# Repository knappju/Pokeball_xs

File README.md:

# __Pokeball_xs__
## __Project Info__

__Created:__                        August 10, 2022

__Project Version:__                v 0.0.0.2  

__Stable Branch:__                  master

### __Code__
* __IDE:__ MPLAB X IDE v5.50

__Last Release Date:__              August 21, 2022  
__Last Stable Release:__            v 0.0.0.2 

### __ECAD__
* __CAD:__ KiCAD v6.0

__Last Release Date:__              August 21, 2022  
__Last Stable Release:__            v 0.0.0.2

## Versioning

For the versions available, see the [tags on this repository](https://github.com/knappju/Pokeball_xs/commits/master). 
## Authors

* **Justin Knapp** - *Circuit Design, PCB Design, Code, Mechanical Design*

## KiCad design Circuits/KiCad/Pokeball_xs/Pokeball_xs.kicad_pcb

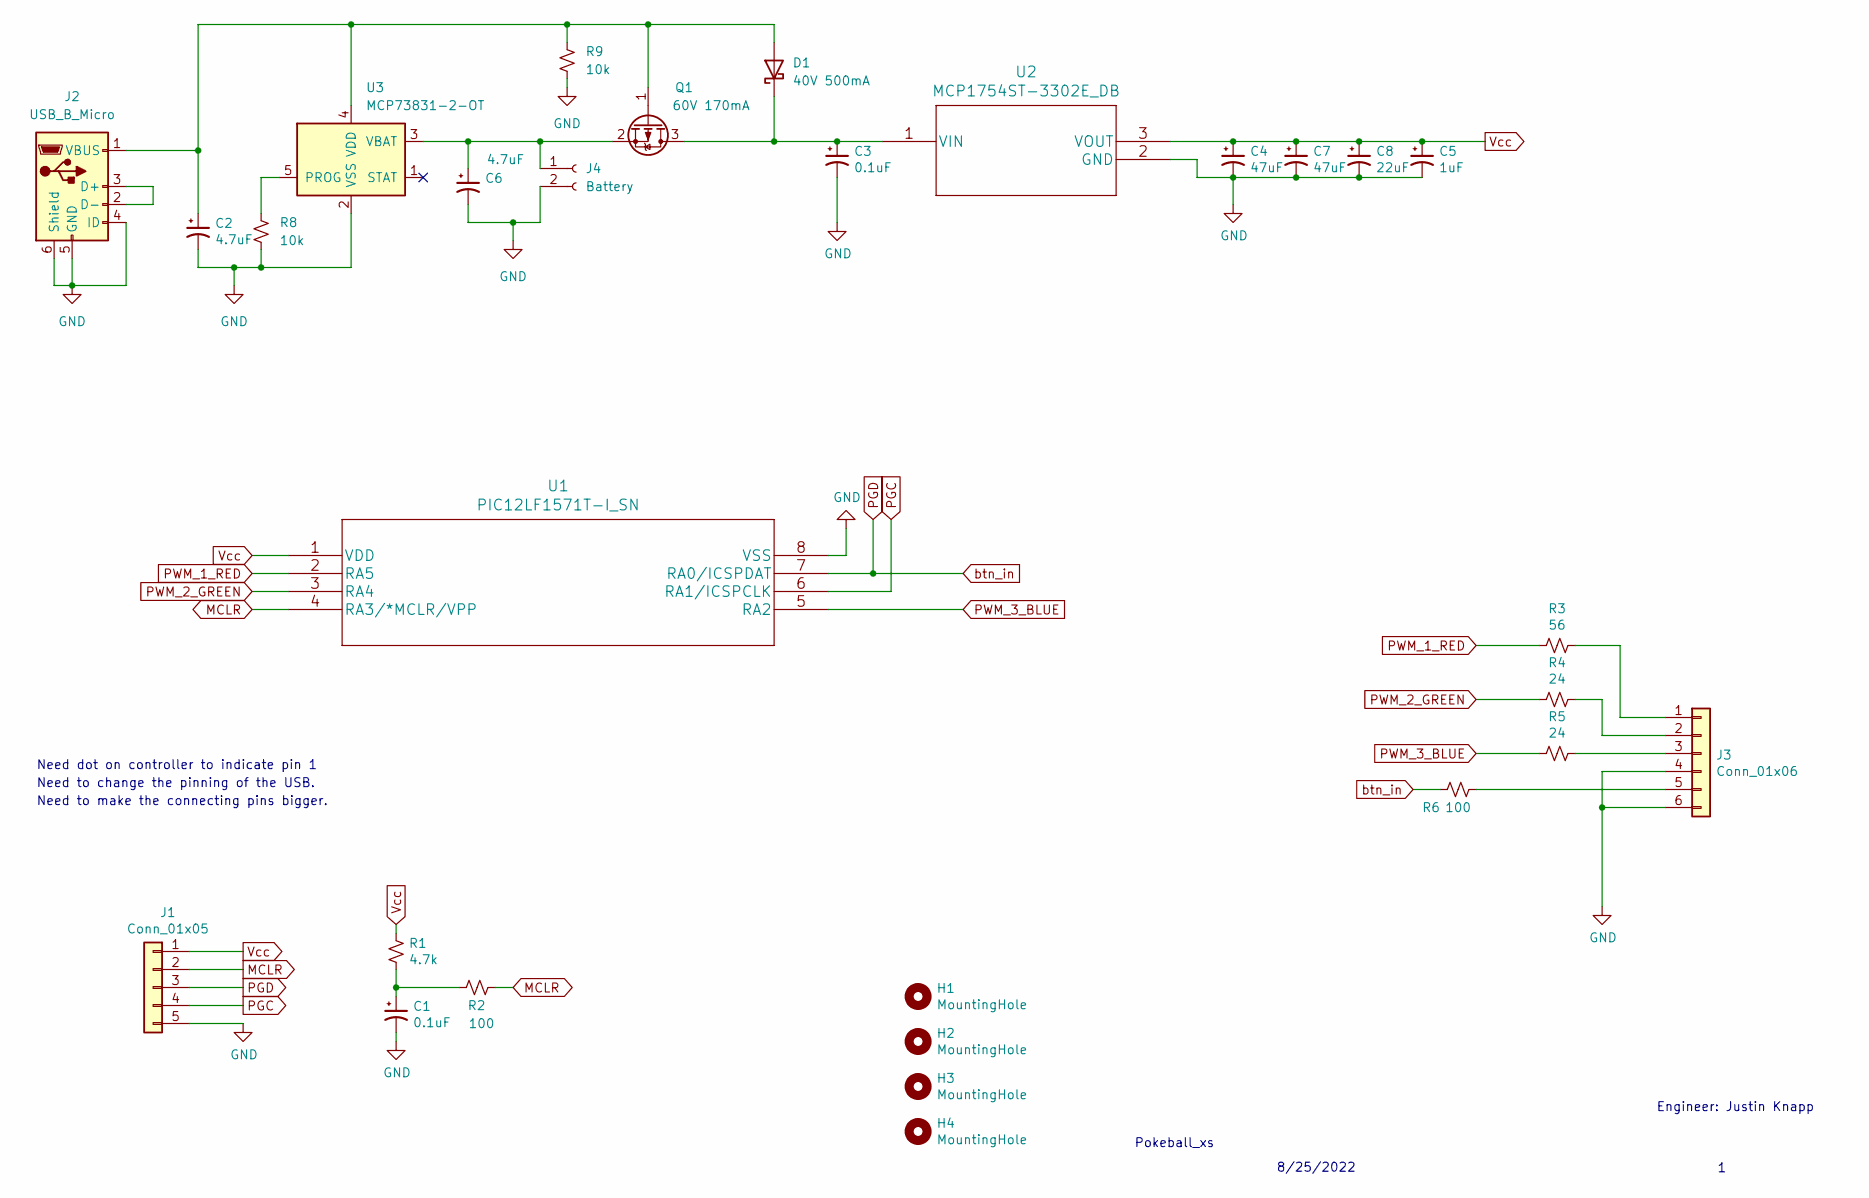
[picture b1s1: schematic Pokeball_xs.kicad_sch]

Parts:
C1, C3: 0.1uF; C_0603_1608Metric
C2, C6: 4.7uF; C_0603_1608Metric
C4, C7: 47uF; C_0603_1608Metric
C5: 1uF; C_0603_1608Metric
C8: 22uF; C_0603_1608Metric
D1: 40V 500mA; D_SOD-123
H1, H2, H3, H4: MountingHole; MountingHole_4.3mm_M4
J1: Conn_01x05; PinHeader_1x05_P2.00mm_Vertical
J2: USB_B_Micro; USB_Micro-B_Molex-105017-0001
J3: Conn_01x06; PinHeader_1x06_P2.00mm_Vertical
J4: Battery; PinSocket_1x02_P2.54mm_Vertical
Q1: 60V 170mA; TSOT-23
R1: 4.7k; R_0603_1608Metric
R2, R6: 100; R_0603_1608Metric
R3: 56; R_0603_1608Metric
R4, R5: 24; R_0603_1608Metric
R8, R9: 10k; R_0603_1608Metric
U1: PIC12LF1571T-I_SN; PIC12LF1571T-I&slash_SN
U2: MCP1754ST-3302E_DB; MCP1754ST-3302E&slash_DB
U3: MCP73831-2-OT; SOT-23-5

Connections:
GND: C1.2, C2.2, C3.2, C4.2, C5.2, C6.2, C7.2, C8.2, J1.5, J2.4 (ID), J2.5 (GND), J2.6 (Shield), J3.4, J3.6, J4.2, R8.2, R9.2, U1.8 (VSS), U2.2 (GND), U3.2 (VSS)
MCLR: J1.2, R2.2, U1.4 (RA3/*MCLR/VPP)
unnamed: C1.1, R1.2, R2.1
unnamed: C2.1, D1.2 (A), J2.1 (VBUS), Q1.1 (G), R9.1, U3.4 (VDD)
unnamed: C3.1, D1.1 (K), Q1.3 (D), U2.1 (VIN)
unnamed: C6.1, J4.1, Q1.2 (S), U3.3 (VBAT)
unnamed: J2.2 (D-), J2.3 (D+)
unnamed: J3.1, R3.1
unnamed: J3.2, R4.1
unnamed: J3.3, R5.1
unnamed: J3.5, R6.1
unnamed: R8.1, U3.5 (PROG)
PGC: J1.4, U1.6 (RA1/ICSPCLK)
PGD: J1.3, R6.2, U1.7 (RA0/ICSPDAT)
PWM_1_RED: R3.2, U1.2 (RA5)
PWM_2_GREEN: R4.2, U1.3 (RA4)
PWM_3_BLUE: R5.2, U1.5 (RA2)
Vcc: C4.1, C5.1, C7.1, C8.1, J1.1, R1.1, U1.1 (VDD), U2.3 (VOUT)

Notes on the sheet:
8/25/2022
Need to change the pinning of the USB.
Need dot on controller to indicate pin 1
Pokeball_xs
Need to make the connecting pins bigger.
Engineer: Justin Knapp

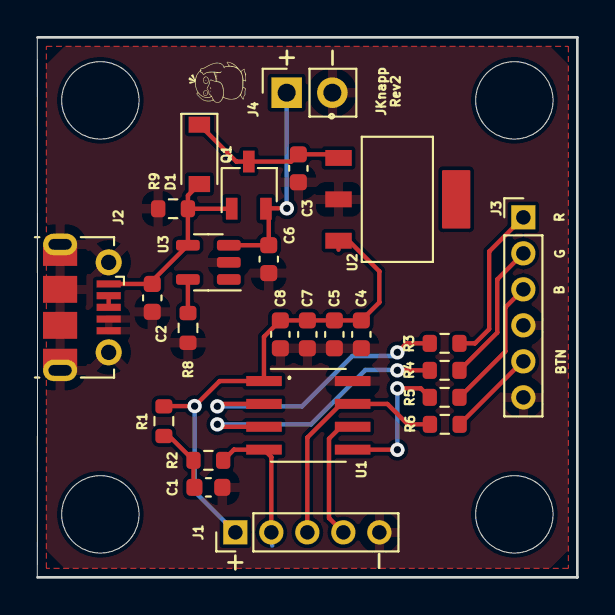
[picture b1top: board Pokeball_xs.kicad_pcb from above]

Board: 2 copper layers, 30.0 x 30.0 mm, 29 parts (0 on the bottom side), 18 nets.

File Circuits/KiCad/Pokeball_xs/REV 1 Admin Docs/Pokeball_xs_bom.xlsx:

Source: | C:\Users\JustinK\Desktop\Pokeball_xs\Circuits\KiCad\Pokeball_xs\Pokeball_xs.kic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
Date: | 44798.49626157407
Tool: | Eeschema (6.0.5)
Generator: | C:\Program Files\KiCad\6.0\bin\scripting\plugins/bom_csv_grouped_by_value.py
Component Count: | 28.0
Individual Components:
Item | Qty | Reference(s) | Value | LibPart | Footprint
 |  | C1 | 0.1uF | Pokeball_xs-rescue:CP1_Small-Device | Capacitor_SMD:C_0603_1608Metric
 |  | C2 | 4.7uF | Pokeball_xs-rescue:CP1_Small-Device | Capacitor_SMD:C_0603_1608Metric
 |  | C3 | 0.1uF | Pokeball_xs-rescue:CP1_Small-Device | Capacitor_SMD:C_0603_1608Metric
 |  | C4 | 22uF | Pokeball_xs-rescue:CP1_Small-Device | Capacitor_SMD:C_0603_1608Metric
 |  | C5 | 1uF | Pokeball_xs-rescue:CP1_Small-Device | Capacitor_SMD:C_0603_1608Metric
 |  | C6 | 4.7uF | Pokeball_xs-rescue:CP1_Small-Device | Capacitor_SMD:C_0603_1608Metric
 |  | D1 | 40V 500mA | Device:D_Schottky | Diode_SMD:D_SOD-123
 |  | H1 | MountingHole | Mechanical:MountingHole | MountingHole:MountingHole_4.3mm_M4
 |  | H2 | MountingHole | Mechanical:MountingHole | MountingHole:MountingHole_4.3mm_M4
 |  | H3 | MountingHole | Mechanical:MountingHole | MountingHole:MountingHole_4.3mm_M4
 |  | H4 | MountingHole | Mechanical:MountingHole | MountingHole:MountingHole_4.3mm_M4
 |  | J1 | Conn_01x05 | Connector_Generic:Conn_01x05 | Connector_PinHeader_1.00mm:PinHeader_1x05_P1.00mm_Vertical
 |  | J2 | USB_B_Micro | Connector:USB_B_Micro | Connector_USB:USB_Micro-AB_Molex_47590-0001
 |  | J3 | Conn_01x06 | Connector_Generic:Conn_01x06 | Connector_PinHeader_1.00mm:PinHeader_1x06_P1.00mm_Vertical
 |  | J4 | Battery | Connector:Conn_01x02_Female | Connector_PinSocket_2.54mm:PinSocket_1x02_P2.54mm_Vertical
 |  | Q1 | 60V 170mA | Device:Q_PMOS_GSD | Package_TO_SOT_SMD:TSOT-23
 |  | R1 | 4.7k | Device:R_Small_US | Resistor_SMD:R_0603_1608Metric
 |  | R2 | 100.0 | Device:R_Small_US | Resistor_SMD:R_0603_1608Metric
 |  | R3 | 56.0 | Device:R_Small_US | Resistor_SMD:R_0603_1608Metric
 |  | R4 | 24.0 | Device:R_Small_US | Resistor_SMD:R_0603_1608Metric
 |  | R5 | 24.0 | Device:R_Small_US | Resistor_SMD:R_0603_1608Metric
 |  | R6 | 100.0 | Device:R_Small_US | Resistor_SMD:R_0603_1608Metric
 |  | R7 | 4.7k | Device:R_Small_US | Resistor_SMD:R_0603_1608Metric
 |  | R8 | 10k | Device:R_Small_US | Resistor_SMD:R_0603_1608Metric
 |  | R9 | 10k | Device:R_Small_US | Resistor_SMD:R_0603_1608Metric
 |  | U1 | PIC12LF1571T-I_SN | Pokeball_xs-rescue:PIC12LF1571T-I_SN-PIC12LF1571T-I-SN | PIC12LF1571T-I_SN:PIC12LF1571T-I&slash_SN
 |  | U2 | MCP1754ST-3302E_DB | Pokeball_xs-rescue:MCP1754ST-3302E_DB-MCP1754ST-3302E-DB | MCP1754ST-3302E_DB:MCP1754ST-3302E&slash_DB
 |  | U3 | MCP73831-2-OT | Battery_Management:MCP73831-2-OT | Package_TO_SOT_SMD:SOT-23-5
Collated Components:
Item | Qty | Reference(s) | Value | LibPart | Footprint | Cost per 1 | Total Cost | Have? | Ordered | Status
1.0 | 2.0 | C1, C3 | 0.1uF | Pokeball_xs-rescue:CP1_Small-Device | Capacitor_SMD:C_0603_1608Metric | 0.0125 | 0.025 | 0 | 1 | PENDING
2.0 | 2.0 | C2, C6 | 4.7uF | Pokeball_xs-rescue:CP1_Small-Device | Capacitor_SMD:C_0603_1608Metric | 0.0246 | 0.0492 | 0 | 1 | PENDING
3.0 | 1.0 | C4 | 22uF | Pokeball_xs-rescue:CP1_Small-Device | Capacitor_SMD:C_0603_1608Metric | 0.133 | 0.133 | 0 | 1 | PENDING
4.0 | 1.0 | C5 | 1uF | Pokeball_xs-rescue:CP1_Small-Device | Capacitor_SMD:C_0603_1608Metric | 0.0146 | 0.0146 | 0 | 1 | PENDING
5.0 | 1.0 | D1 | 40V 500mA | Device:D_Schottky | Diode_SMD:D_SOD-123 | 0.177 | 0.177 | 1 | 0 | GOOD
6.0 | 4.0 | H1, H2, H3, H4 | MountingHole | Mechanical:MountingHole | MountingHole:MountingHole_4.3mm_M4 | 0.0 | 0 | 0 | 0 | NEEDS ORDERING
7.0 | 1.0 | J1 | Conn_01x05 | Connector_Generic:Conn_01x05 | Connector_PinHeader_1.00mm:PinHeader_1x05_P1.00mm_Vertical | 0.0 | 0 | 0 | 0 | NEEDS ORDERING
8.0 | 1.0 | J2 | USB_B_Micro | Connector:USB_B_Micro | Connector_USB:USB_Micro-AB_Molex_47590-0001 | 0.86 | 0.86 | 0 | 1 | PENDING
9.0 | 1.0 | J3 | Conn_01x06 | Connector_Generic:Conn_01x06 | Connector_PinHeader_1.00mm:PinHeader_1x06_P1.00mm_Vertical | 0.0 | 0 | 0 | 0 | NEEDS ORDERING
10.0 | 1.0 | J4 | Battery | Connector:Conn_01x02_Female | Connector_PinSocket_2.54mm:PinSocket_1x02_P2.54mm_Vertical | 0.0 | 0 | 0 | 0 | NEEDS ORDERING
11.0 | 1.0 | Q1 | 60V 170mA | Device:Q_PMOS_GSD | Package_TO_SOT_SMD:TSOT-23 | 0.343 | 0.343 | 1 | 0 | GOOD
12.0 | 2.0 | R1, R7 | 4.7k | Device:R_Small_US | Resistor_SMD:R_0603_1608Metric | 0.0394 | 0.0788 | 0 | 1 | PENDING
13.0 | 2.0 | R2, R6 | 100.0 | Device:R_Small_US | Resistor_SMD:R_0603_1608Metric | 0.0184 | 0.0368 | 0 | 1 | PENDING
14.0 | 1.0 | R3 | 56.0 | Device:R_Small_US | Resistor_SMD:R_0603_1608Metric | 0.05 | 0.05 | 0 | 1 | PENDING
15.0 | 2.0 | R4, R5 | 24.0 | Device:R_Small_US | Resistor_SMD:R_0603_1608Metric | 0.05 | 0.1 | 0 | 1 | PENDING
16.0 | 2.0 | R8, R9 | 10k | Device:R_Small_US | Resistor_SMD:R_0603_1608Metric | 0.0184 | 0.0368 | 0 | 1 | PENDING
17.0 | 1.0 | U1 | PIC12LF1571T-I_SN | Pokeball_xs-rescue:PIC12LF1571T-I_SN-PIC12LF1571T-I-SN | PIC12LF1571T-I_SN:PIC12LF1571T-I&slash_SN | 0.79 | 0.79 | 1 | 0 | GOOD
18.0 | 1.0 | U2 | MCP1754ST-3302E_DB | Pokeball_xs-rescue:MCP1754ST-3302E_DB-MCP1754ST-3302E-DB | MCP1754ST-3302E_DB:MCP1754ST-3302E&slash_DB | 0.84 | 0.84 | 1 | 0 | GOOD
19.0 | 1.0 | U3 | MCP73831-2-OT | Battery_Management:MCP73831-2-OT | Package_TO_SOT_SMD:SOT-23-5 | 0.76 | 0.76 | 1 | 0 | GOOD
 |  |  |  |  |  |  | 4.2942

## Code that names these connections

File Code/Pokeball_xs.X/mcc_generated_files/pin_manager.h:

/**
  @Generated Pin Manager Header File

  @Company:
    Microchip Technology Inc.

  @File Name:
    pin_manager.h

  @Summary:
    This is the Pin Manager file generated using PIC10 / PIC12 / PIC16 / PIC18 MCUs

  @Description
    This header file provides APIs for driver for .
    Generation Information :
        Product Revision  :  PIC10 / PIC12 / PIC16 / PIC18 MCUs - 1.81.7
        Device            :  PIC12LF1571
        Driver Version    :  2.11
    The generated drivers are tested against the following:
        Compiler          :  XC8 2.31 and above
        MPLAB 	          :  MPLAB X 5.45	
*/

/*
    (c) 2018 Microchip Technology Inc. and its subsidiaries. 
    
    Subject to your compliance with these terms, you may use Microchip software and any 
    derivatives exclusively with Microchip products. It is your responsibility to comply with third party 
    license terms applicable to your use of third party software (including open source software) that 
    may accompany Microchip software.
    
    THIS SOFTWARE IS SUPPLIED BY MICROCHIP "AS IS". NO WARRANTIES, WHETHER 
    EXPRESS, IMPLIED OR STATUTORY, APPLY TO THIS SOFTWARE, INCLUDING ANY 
    IMPLIED WARRANTIES OF NON-INFRINGEMENT, MERCHANTABILITY, AND FITNESS 
    FOR A PARTICULAR PURPOSE.
    
    IN NO EVENT WILL MICROCHIP BE LIABLE FOR ANY INDIRECT, SPECIAL, PUNITIVE, 
    INCIDENTAL OR CONSEQUENTIAL LOSS, DAMAGE, COST OR EXPENSE OF ANY KIND 
    WHATSOEVER RELATED TO THE SOFTWARE, HOWEVER CAUSED, EVEN IF MICROCHIP 
    HAS BEEN ADVISED OF THE POSSIBILITY OR THE DAMAGES ARE FORESEEABLE. TO 
    THE FULLEST EXTENT ALLOWED BY LAW, MICROCHIP'S TOTAL LIABILITY ON ALL 
    CLAIMS IN ANY WAY RELATED TO THIS SOFTWARE WILL NOT EXCEED THE AMOUNT 
    OF FEES, IF ANY, THAT YOU HAVE PAID DIRECTLY TO MICROCHIP FOR THIS 
    SOFTWARE.
*/

#ifndef PIN_MANAGER_H
#define PIN_MANAGER_H

/**
  Section: Included Files
*/

#include <xc.h>

#define INPUT   1
#define OUTPUT  0

#define HIGH    1
#define LOW     0

#define ANALOG      1
#define DIGITAL     0

#define PULL_UP_ENABLED      1
#define PULL_UP_DISABLED     0

// get/set BTN_IN aliases
#define BTN_IN_TRIS                 TRISAbits.TRISA0
#define BTN_IN_LAT                  LATAbits.LATA0
#define BTN_IN_PORT                 PORTAbits.RA0
#define BTN_IN_WPU                  WPUAbits.WPUA0
#define BTN_IN_OD                   ODCONAbits.ODA0
#define BTN_IN_ANS                  ANSELAbits.ANSA0
#define BTN_IN_SetHigh()            do { LATAbits.LATA0 = 1; } while(0)
#define BTN_IN_SetLow()             do { LATAbits.LATA0 = 0; } while(0)
#define BTN_IN_Toggle()             do { LATAbits.LATA0 = ~LATAbits.LATA0; } while(0)
#define BTN_IN_GetValue()           PORTAbits.RA0
#define BTN_IN_SetDigitalInput()    do { TRISAbits.TRISA0 = 1; } while(0)
#define BTN_IN_SetDigitalOutput()   do { TRISAbits.TRISA0 = 0; } while(0)
#define BTN_IN_SetPullup()          do { WPUAbits.WPUA0 = 1; } while(0)
#define BTN_IN_ResetPullup()        do { WPUAbits.WPUA0 = 0; } while(0)
#define BTN_IN_SetPushPull()        do { ODCONAbits.ODA0 = 0; } while(0)
#define BTN_IN_SetOpenDrain()       do { ODCONAbits.ODA0 = 1; } while(0)
#define BTN_IN_SetAnalogMode()      do { ANSELAbits.ANSA0 = 1; } while(0)
#define BTN_IN_SetDigitalMode()     do { ANSELAbits.ANSA0 = 0; } while(0)

// get/set RA2 procedures
#define RA2_SetHigh()            do { LATAbits.LATA2 = 1; } while(0)
#define RA2_SetLow()             do { LATAbits.LATA2 = 0; } while(0)
#define RA2_Toggle()             do { LATAbits.LATA2 = ~LATAbits.LATA2; } while(0)
#define RA2_GetValue()              PORTAbits.RA2
#define RA2_SetDigitalInput()    do { TRISAbits.TRISA2 = 1; } while(0)
#define RA2_SetDigitalOutput()   do { TRISAbits.TRISA2 = 0; } while(0)
#define RA2_SetPullup()             do { WPUAbits.WPUA2 = 1; } while(0)
#define RA2_ResetPullup()           do { WPUAbits.WPUA2 = 0; } while(0)
#define RA2_SetAnalogMode()         do { ANSELAbits.ANSA2 = 1; } while(0)
#define RA2_SetDigitalMode()        do { ANSELAbits.ANSA2 = 0; } while(0)

// get/set RA4 procedures
#define RA4_SetHigh()            do { LATAbits.LATA4 = 1; } while(0)
#define RA4_SetLow()             do { LATAbits.LATA4 = 0; } while(0)
#define RA4_Toggle()             do { LATAbits.LATA4 = ~LATAbits.LATA4; } while(0)
#define RA4_GetValue()              PORTAbits.RA4
#define RA4_SetDigitalInput()    do { TRISAbits.TRISA4 = 1; } while(0)
#define RA4_SetDigitalOutput()   do { TRISAbits.TRISA4 = 0; } while(0)
#define RA4_SetPullup()             do { WPUAbits.WPUA4 = 1; } while(0)
#define RA4_ResetPullup()           do { WPUAbits.WPUA4 = 0; } while(0)
#define RA4_SetAnalogMode()         do { ANSELAbits.ANSA4 = 1; } while(0)
#define RA4_SetDigitalMode()        do { ANSELAbits.ANSA4 = 0; } while(0)

// get/set RA5 procedures
#define RA5_SetHigh()            do { LATAbits.LATA5 = 1; } while(0)
#define RA5_SetLow()             do { LATAbits.LATA5 = 0; } while(0)
#define RA5_Toggle()             do { LATAbits.LATA5 = ~LATAbits.LATA5; } while(0)
#define RA5_GetValue()              PORTAbits.RA5
#define RA5_SetDigitalInput()    do { TRISAbits.TRISA5 = 1; } while(0)
#define RA5_SetDigitalOutput()   do { TRISAbits.TRISA5 = 0; } while(0)
#define RA5_SetPullup()             do { WPUAbits.WPUA5 = 1; } while(0)
#define RA5_ResetPullup()           do { WPUAbits.WPUA5 = 0; } while(0)

/**
   @Param
    none
   @Returns
    none
   @Description
    GPIO and peripheral I/O initialization
   @Example
    PIN_MANAGER_Initialize();
 */
void PIN_MANAGER_Initialize (void);

/**
 * @Param
    none
 * @Returns
    none
 * @Description
    Interrupt on Change Handling routine
 * @Example
    PIN_MANAGER_IOC();
 */
void PIN_MANAGER_IOC(void);



#endif // PIN_MANAGER_H
/**
 End of File
*/

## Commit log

2022-08-10 v 0.0.0.0 - init project commit
2022-08-19 v 0.0.0.1 - Include the charging circuit on the PCB
2022-08-21 v 0.0.0.2 - Testing the pwm output on the switch. Creation of the README.md.
2022-08-23 v 0.0.0.3 - updates to the board and the mechanical system.
2022-08-24 v 0.0.0.4 - submit rev 1 of the pokeball to pcbway.
2022-08-26 v 0.0.0.5 - updates to some circuit admin stuff
2022-09-07 v 0.0.0.6 - Testing the circuit
2022-09-07 v 0.0.0.7 - add the mechanical
2022-10-03 v 0.0.0.8 - Board submitted to pcbway
2022-10-13 v 1.0.0.0 - minimum working product.
2022-10-14 v 1.0.0.1 - A better ball
2022-10-24 v 1.0.0.2 - make sure everything is backed up

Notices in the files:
parts and their libraries:
Copyright 2021 Accelerated Designs. All rights reserved.
